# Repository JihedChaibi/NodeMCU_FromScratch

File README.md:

# NodeMCU_FromScratch
### Costumize your NodeMCU board  

Coming soon : Full documentation + components list files..

![Image of nucleo](
https://github.com/JihedChaibi/NodeMCU_FromScratch/blob/master/NodeMCU_KiCad.PNG)

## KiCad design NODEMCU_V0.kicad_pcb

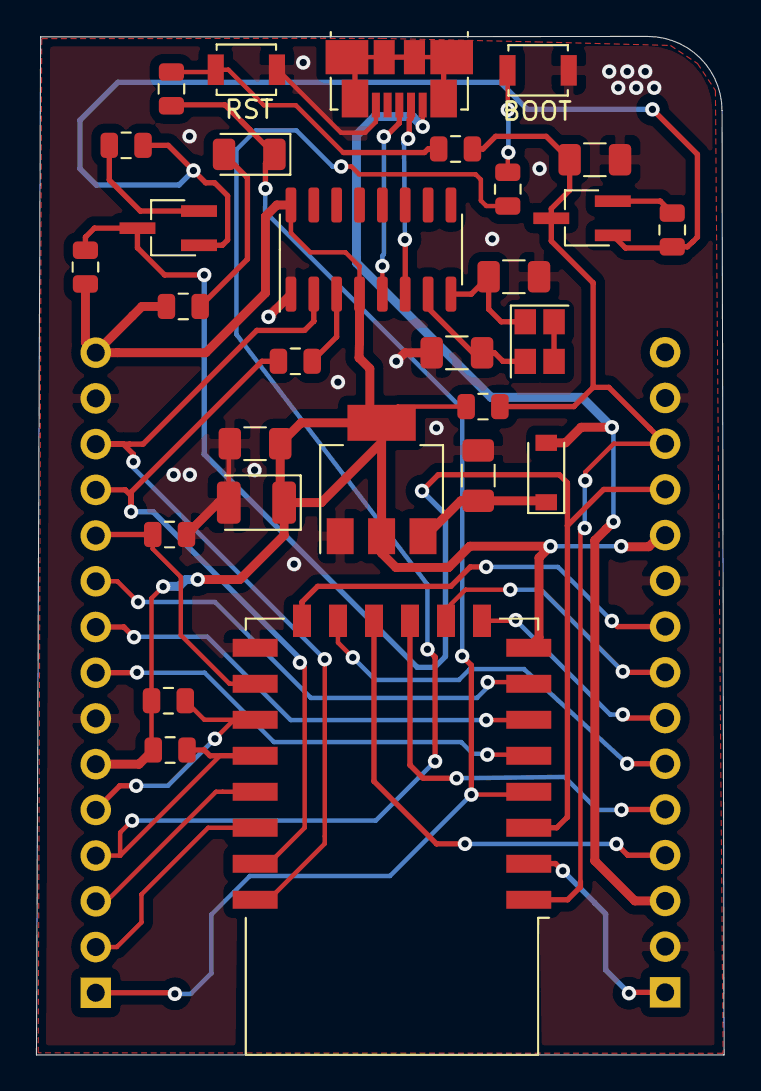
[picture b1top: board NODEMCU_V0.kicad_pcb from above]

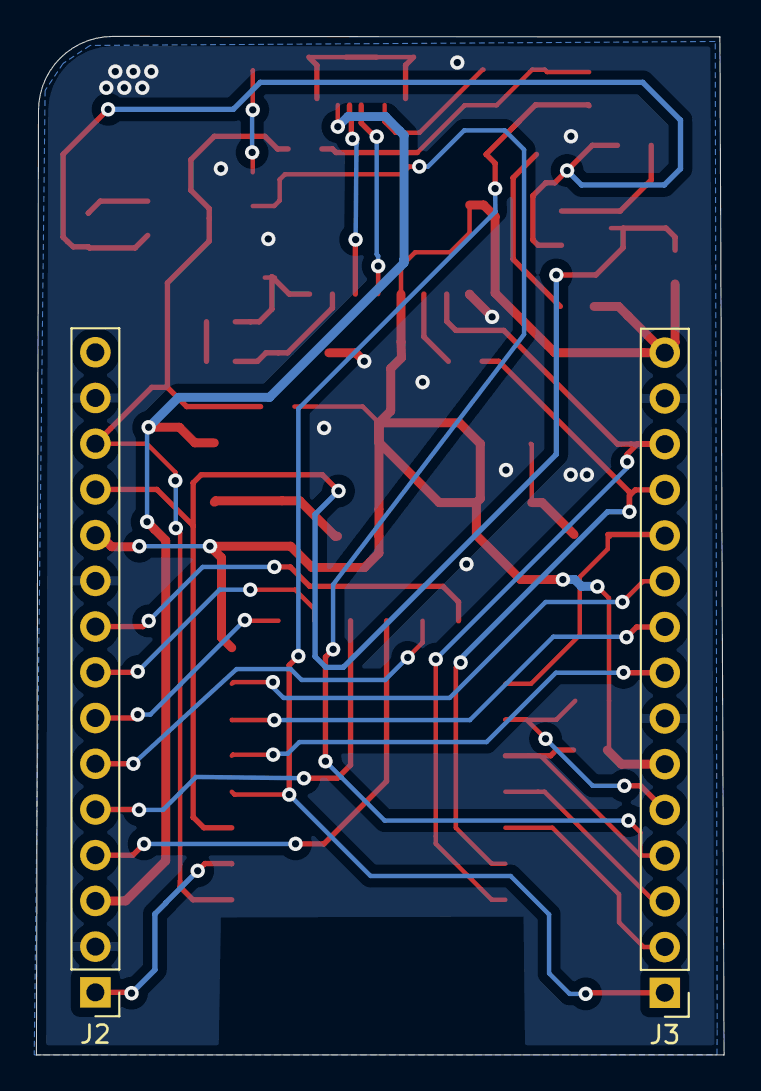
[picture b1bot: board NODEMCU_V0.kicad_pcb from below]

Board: 2 copper layers, 38.2 x 56.6 mm, 31 parts (2 on the bottom side), 35 nets.

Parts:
BOOT: SW_Push; SW_SPST_B3U-1000P
C1, C2, C3, C4, C5: C; C_1206_3216Metric
CPP1: CP; CP_EIA-3528-21_Kemet-B
D1: 1N5819; D_SOD-123
D2: LED; LED_1206_3216Metric
J1: USB_B_Micro; USB_Micro-B_Molex_47346-0001
J2, J3: Conn_01x15_Male; PinHeader_1x15_P2.54mm_Vertical
Q0, Q1: S8050; TSOT-23_HandSoldering
R1, R2, R3, R4, R5, R6, R7, R8, R9, R10, R11, R12: R; R_0805_2012Metric
RST: SW_Push; SW_SPST_B3U-1000P
U1: NCP1117-3.3_SOT223; SOT-223-3_TabPin2
U2: CH340G; SOIC-16_3.9x9.9mm_P1.27mm
U3: ESP-12E
Y1: Crystal; Crystal_SMD_SeikoEpson_FA238-4Pin_3.2x2.5mm

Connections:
3V3: C4.1, CPP1.1, J2.11, J3.6, J3.15, R1.2, R2.2, R3.2, R4.2, R6.1, U1.2, U2.4, U2.16, U3.8
5V: C1.1, D1.1, U1.3
ADC: J2.1, U3.2
CS: J2.7, U3.9
D+: J1.3, U2.5
D-: J1.2, U2.6
DTR: Q0.1, Q1.1, R10.1, R11.1
EN: J2.12, Q0.3, R3.1, U3.3
GND: BOOT.2, C1.2, C2.2, C3.2, C4.2, C5.2, CPP1.2, J1.5, J2.2, J2.10, J2.14, J3.7, J3.14, R5.2, RST.2, U1.1, U2.1, U3.15
GPIO0: J3.4, R1.1, R9.1, U3.18
GPIO2: J3.5, R2.1, U3.17
GPIO4: J3.3, U3.19
GPIO5: J3.2, U3.20
GPIO9: J2.5, U3.11
GPIO10: J2.4, U3.12
GPIO12: J3.9, U3.6
GPIO13: J3.10, U3.7
GPIO14: J3.8, U3.5
GPIO15: J3.11, R5.1, U3.16
GPIO16: D2.1, J3.1, R7.1, U3.4
MISO: J2.8, U3.10
MOSI: J2.6, U3.13
unnamed: C2.1, U2.7, Y1.2
unnamed: C3.1, U2.8, Y1.1
unnamed: D2.2, R6.2
unnamed: Q0.2, R11.2
unnamed: Q1.2, R10.2
unnamed: R7.2, R8.2, RST.1
unnamed: BOOT.1, R9.2
unnamed: R12.2, U2.3
RXD: J3.12, R12.1, U3.21
SCK: J2.9, U3.14
TXD: J3.13, U2.2, U3.22
VUSB: D1.2, J1.1, J2.3
nRST: C5.1, J2.13, Q1.3, R4.1, R8.1, U3.1

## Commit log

2020-09-05 Rename NODEMCU_V0.kicad_pcb to KiCad_Files/NODEMCU_V0.kicad_pcb
2020-09-05 Rename NODEMCU_V0.net to KiCad_Files/NODEMCU_V0.net
2020-09-05 Rename NODEMCU_V0.pro to KiCad_Files/NODEMCU_V0.pro
2020-09-05 Rename NODEMCU_V0.sch to KiCad_Files/NODEMCU_V0.sch
